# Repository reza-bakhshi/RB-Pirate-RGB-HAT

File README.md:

<div align="center">

# RB-Pirate RGB & Button HAT

**Optional RGB lighting and physical-button expansion for RB-Pirate**

</div>

RB-Pirate RGB & Button HAT adds programmable RGB visual feedback and a physical
user button to the [RB-Pirate](https://github.com/reza-bakhshi/RB-Pirate)
hardware debugging tool. It enables status lighting, animations, button-based
mode control, and scriptable user input through the RB-Pirate firmware.

The HAT is completely optional. RB-Pirate remains fully functional without it,
so the expansion can be installed only when visual feedback or a physical
button is useful.

## PCB gallery

<table>
  <tr>
    <th width="50%">Top</th>
    <th width="50%">Bottom</th>
  </tr>
  <tr>
    <td></td>
    <td></td>
  </tr>
</table>

## Hardware features

- 16 individually addressable SK6812 RGB LEDs arranged around the board
- Side-facing LEDs for perimeter lighting and visual effects
- One 100 nF local decoupling capacitor for each RGB LED
- Large central momentary push button
- Dedicated RGB data and button signals
- Compact four-pin, 2.54 mm SMD connection to RB-Pirate
- Four mounting holes for mechanical alignment
- Two-layer, 1.6 mm PCB
- KiCad 10 schematic and PCB design files

## Firmware features

When used with the
[custom RB-Pirate firmware](https://github.com/reza-bakhshi/RB-Pirate-Firmware),
the HAT provides:

- RGB status indication
- Startup and activity animations
- Introduction and party-mode effects
- Physical escape and mode-control input
- Scriptable button input for automation and custom workflows

## Connector pinout

The HAT connects to RB-Pirate through connector **J1**.

| Pin | Signal | Description |
|:---:|---|---|
| 1 | RGB_IN | Serial data input for the SK6812 LED chain |
| 2 | BUTTON | User-button signal to RB-Pirate |
| 3 | VDD / VUSB | Power input for the HAT |
| 4 | GND | Ground |

> [!NOTE]
> Power off RB-Pirate before installing or removing the HAT. Check connector
> orientation and pin alignment before applying power.

## Related projects

- [RB-Pirate hardware](https://github.com/reza-bakhshi/RB-Pirate)
- [RB-Pirate firmware](https://github.com/reza-bakhshi/RB-Pirate-Firmware)

## License

This project is released under the [MIT License](LICENSE).

Third-party symbols, footprints, models, and other bundled resources remain
subject to their respective licenses.

---

<div align="center">
  <sub>Optional light and button control for the RB-Pirate ecosystem.</sub>
</div>

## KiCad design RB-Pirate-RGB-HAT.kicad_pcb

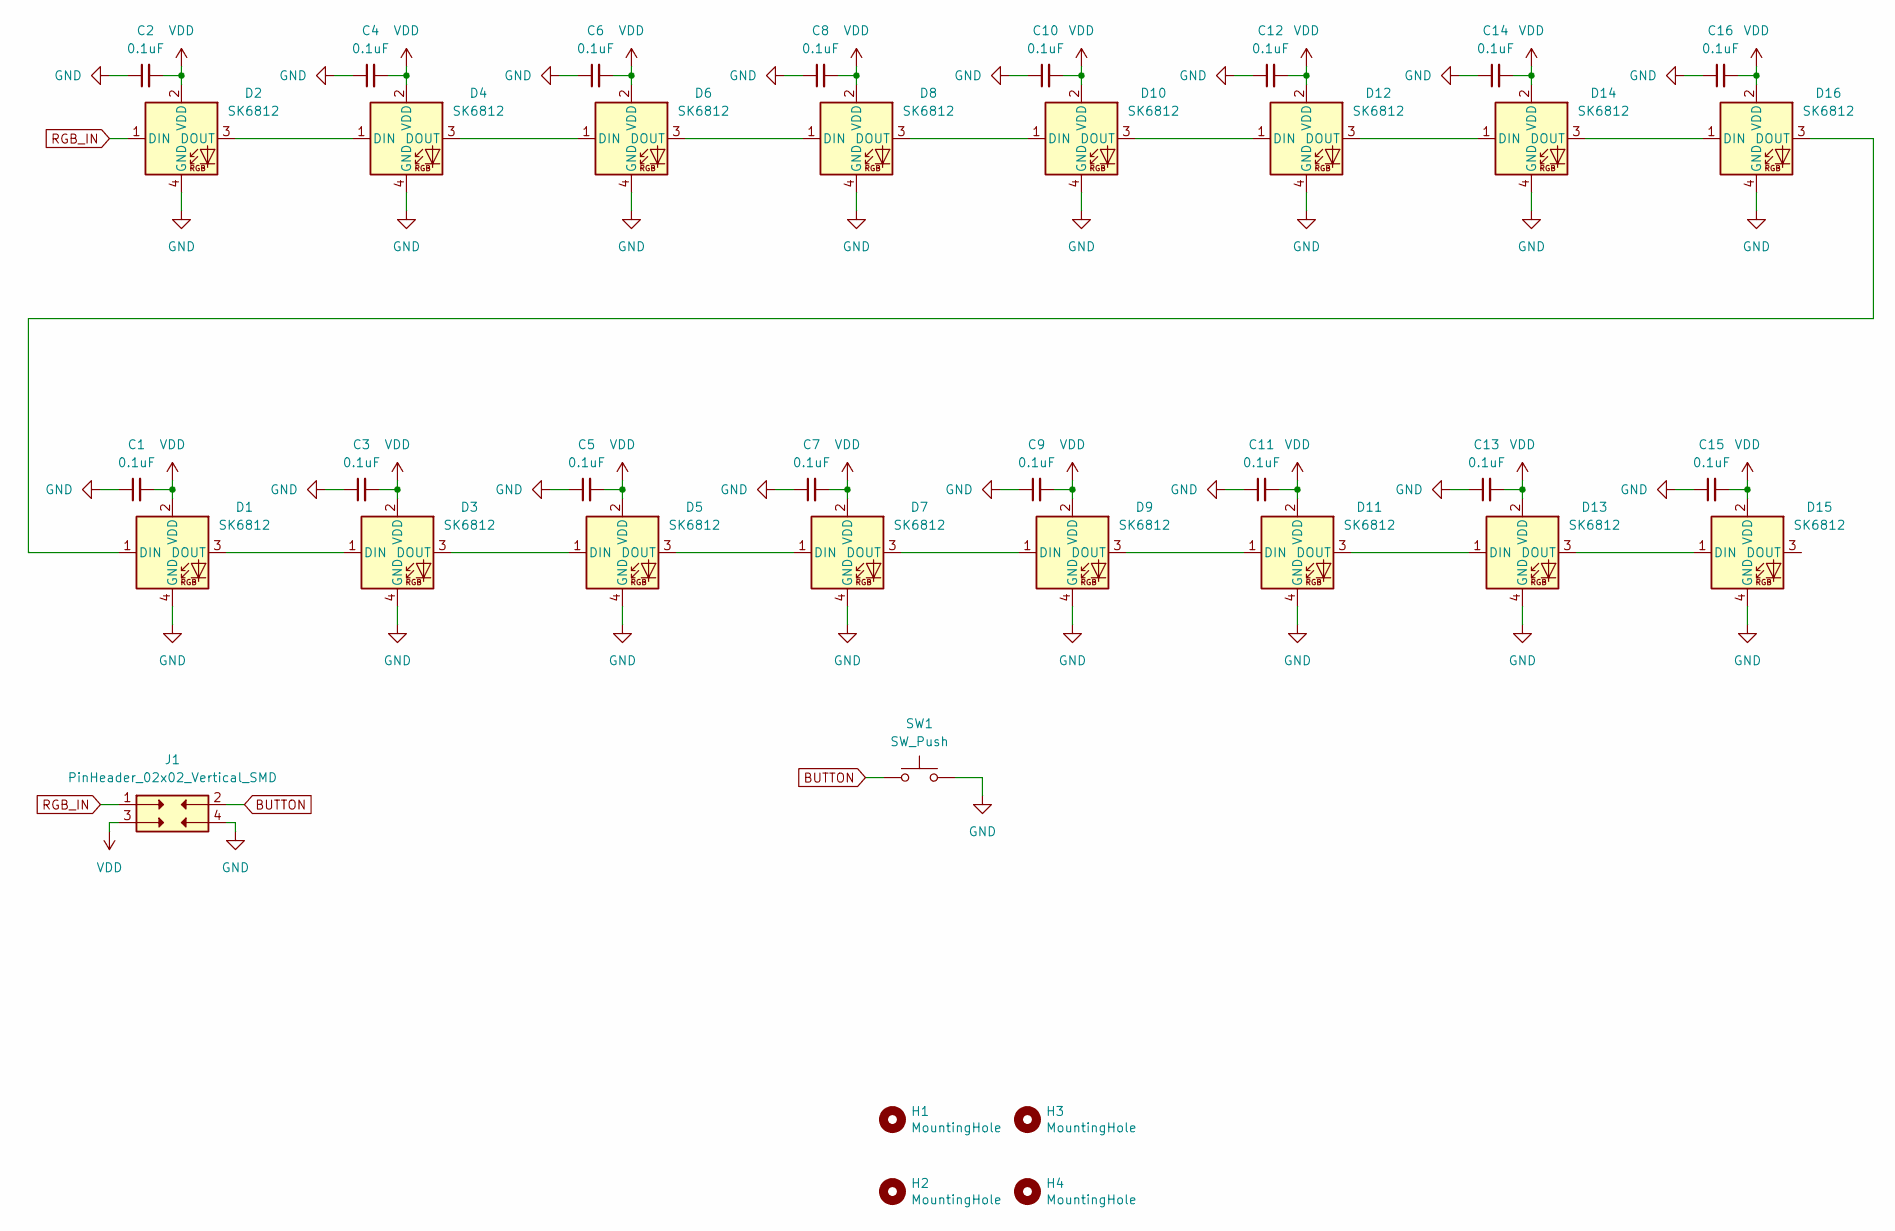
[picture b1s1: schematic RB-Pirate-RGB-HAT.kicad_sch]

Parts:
C1, C2, C3, C4, C5, C6, C7, C8, C9, C10, C11, C12, C13, C14, C15, C16: 0.1uF; C_0402_1005Metric; Voltage 16V; Tolerance 10%
D1, D2, D3, D4, D5, D6, D7, D8, D9, D10, D11, D12, D13, D14, D15, D16: SK6812; SK6812-side-a
H1, H2, H3, H4: MountingHole; MountingHole_3.2mm_M3
J1: PinHeader_02x02_Vertical_SMD; PinSocket_2x02_P2.54mm_Vertical_SMD
SW1: SW_Push; Push_Button_W12mm

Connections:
BUTTON: J1.2, SW1.1
GND: C1.1, C2.1, C3.1, C4.1, C5.1, C6.1, C7.1, C8.1, C9.1, C10.1, C11.1, C12.1, C13.1, C14.1, C15.1, C16.1, D1.4 (GND), D2.4 (GND), D3.4 (GND), D4.4 (GND), D5.4 (GND), D6.4 (GND), D7.4 (GND), D8.4 (GND), D9.4 (GND), D10.4 (GND), D11.4 (GND), D12.4 (GND), D13.4 (GND), D14.4 (GND), D15.4 (GND), D16.4 (GND), J1.4, SW1.2
unnamed: D1.1 (DIN), D16.3 (DOUT)
unnamed: D1.3 (DOUT), D3.1 (DIN)
unnamed: D2.3 (DOUT), D4.1 (DIN)
unnamed: D3.3 (DOUT), D5.1 (DIN)
unnamed: D4.3 (DOUT), D6.1 (DIN)
unnamed: D5.3 (DOUT), D7.1 (DIN)
unnamed: D6.3 (DOUT), D8.1 (DIN)
unnamed: D7.3 (DOUT), D9.1 (DIN)
unnamed: D8.3 (DOUT), D10.1 (DIN)
unnamed: D10.3 (DOUT), D12.1 (DIN)
unnamed: D9.3 (DOUT), D11.1 (DIN)
unnamed: D11.3 (DOUT), D13.1 (DIN)
unnamed: D12.3 (DOUT), D14.1 (DIN)
unnamed: D13.3 (DOUT), D15.1 (DIN)
unnamed: D14.3 (DOUT), D16.1 (DIN)
RGB_IN: D2.1 (DIN), J1.1
VDD: C1.2, C2.2, C3.2, C4.2, C5.2, C6.2, C7.2, C8.2, C9.2, C10.2, C11.2, C12.2, C13.2, C14.2, C15.2, C16.2, D1.2 (VDD), D2.2 (VDD), D3.2 (VDD), D4.2 (VDD), D5.2 (VDD), D6.2 (VDD), D7.2 (VDD), D8.2 (VDD), D9.2 (VDD), D10.2 (VDD), D11.2 (VDD), D12.2 (VDD), D13.2 (VDD), D14.2 (VDD), D15.2 (VDD), D16.2 (VDD), J1.3

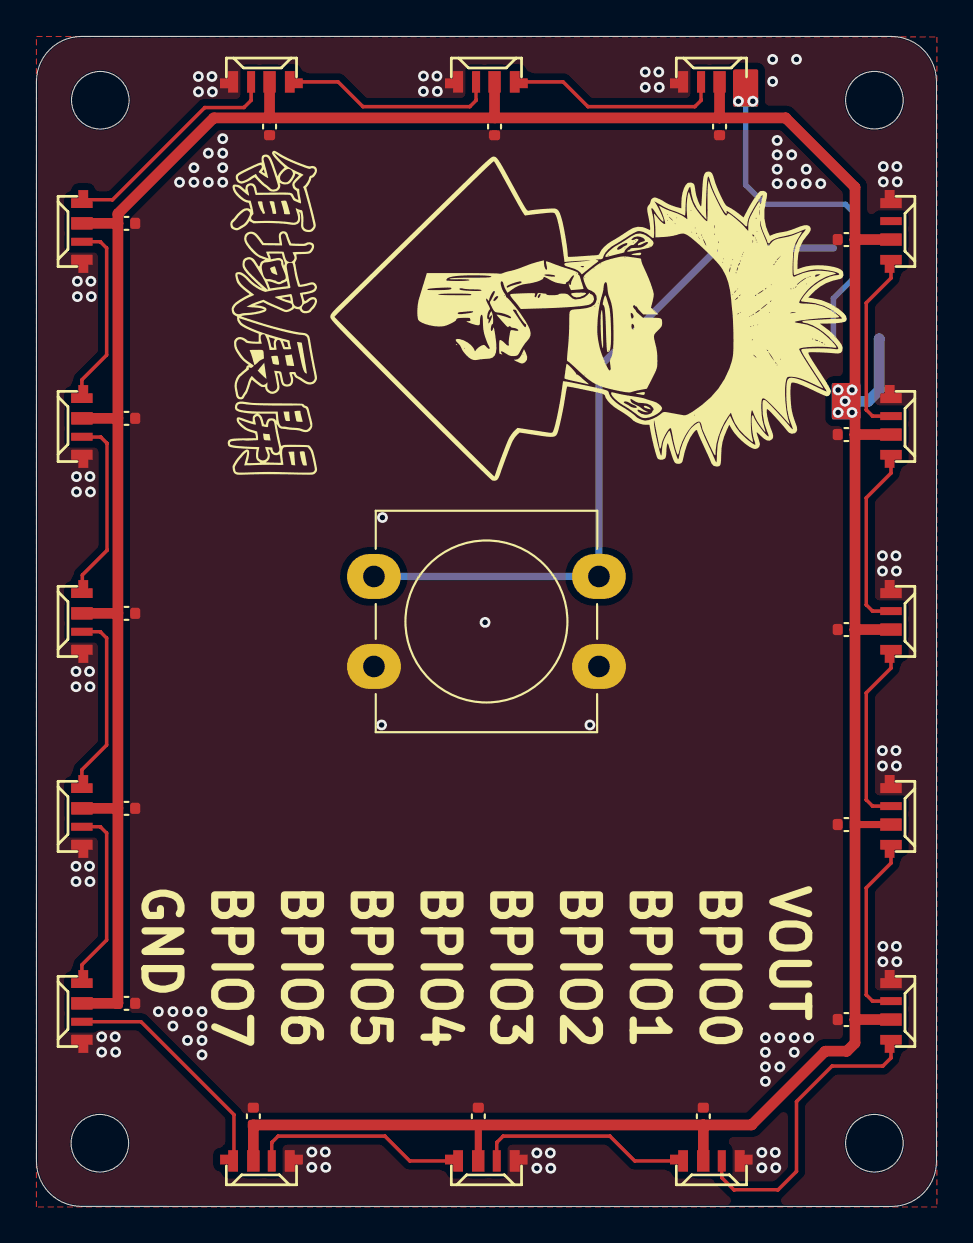
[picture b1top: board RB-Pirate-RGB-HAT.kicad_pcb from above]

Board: 2 copper layers, 50.0 x 65.0 mm, 38 parts (1 on the bottom side), 19 nets.

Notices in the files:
README.md:
License: MIT
